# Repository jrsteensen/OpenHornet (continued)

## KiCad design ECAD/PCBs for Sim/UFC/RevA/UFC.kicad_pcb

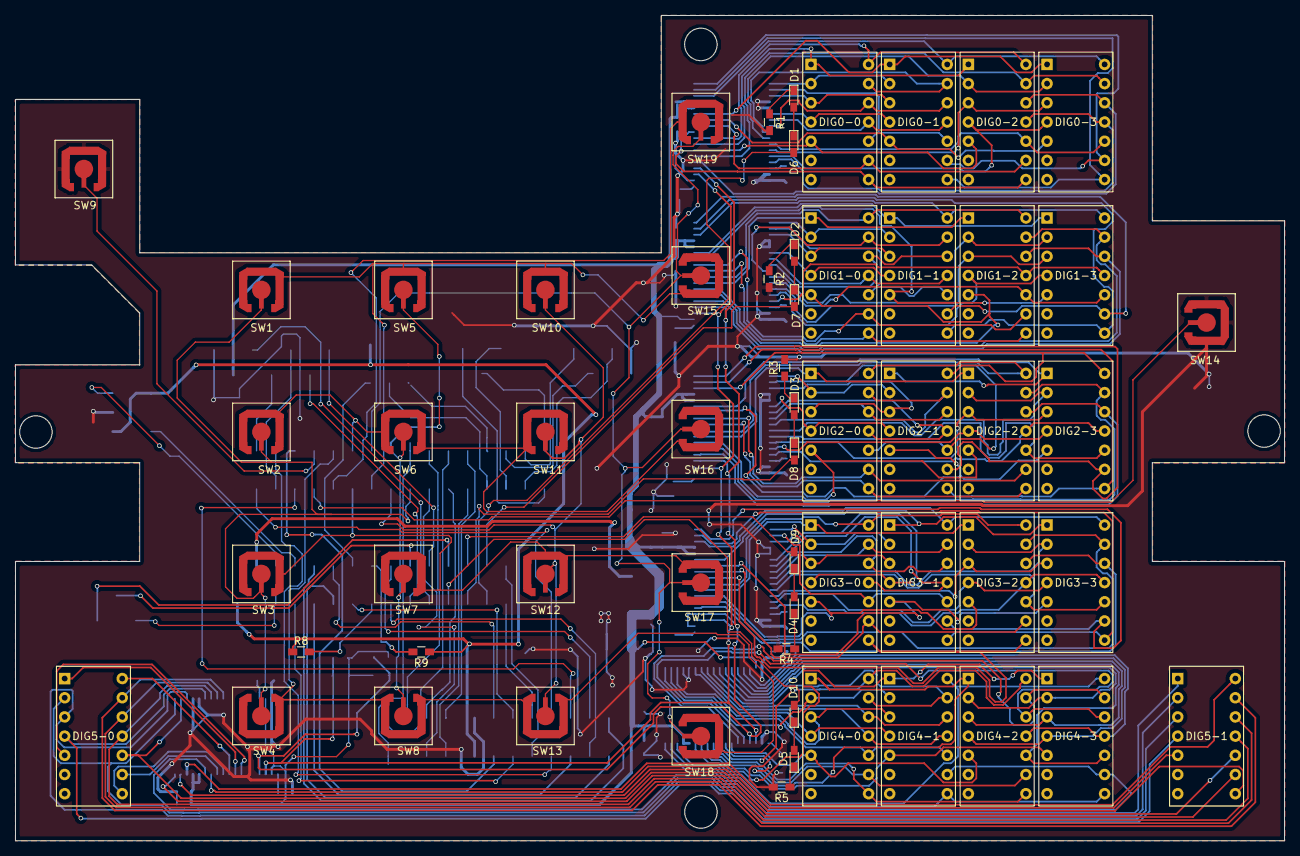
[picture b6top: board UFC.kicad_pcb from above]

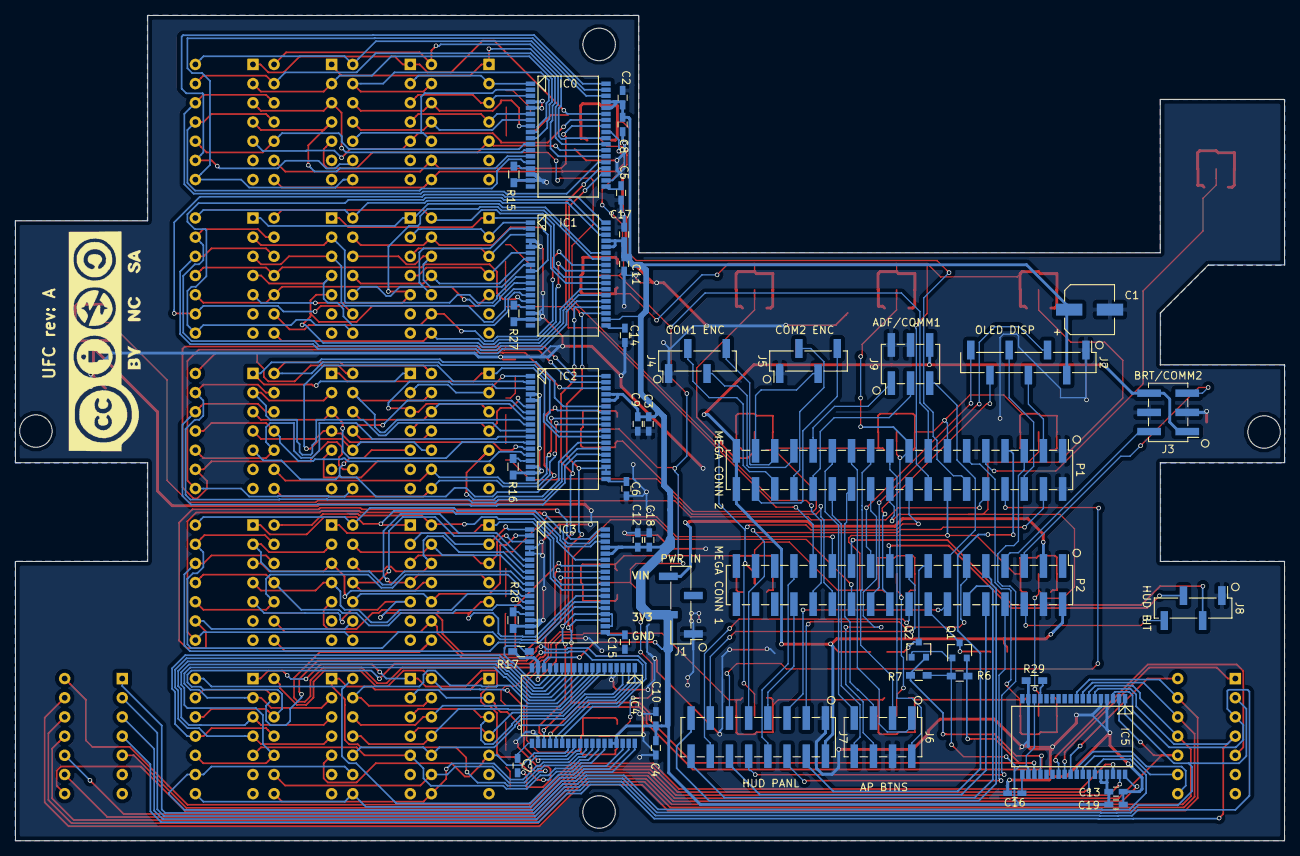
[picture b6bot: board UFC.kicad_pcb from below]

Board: 2 copper layers, 168.0 x 109.2 mm, 108 parts (46 on the bottom side), 223 nets.

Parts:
C1: 220uF; CP_Elec_6.3x7.7
C2, C3, C4, C11, C12, C13: 47uF; C_0603_HandSoldering
C5, C6, C7, C14, C15, C16: 27pF; C_0603_HandSoldering
C8, C9, C10, C17, C18, C19: 100nF; C_0603_HandSoldering
D1, D2, D3, D4, D5, D6, D7, D8, D9, D10: WP914GDT; LED_0603_HandSoldering
DIG0-0, DIG0-1, DIG0-2, DIG0-3, DIG1-0, DIG1-1, DIG1-2, DIG1-3, DIG2-0, DIG2-1, DIG2-2, DIG2-3, DIG3-0, DIG3-1, DIG3-2, DIG3-3, DIG4-0, DIG4-1, DIG4-2, DIG4-3, DIG5-0, DIG5-1: LTP-305G
IC0, IC1, IC2, IC3, IC4, IC5: MAX6953
J1: PWR IN; Pin_Header_Straight_1x04_Pitch2.54mm_SMD_Pin1Left
J2: OLED DISP; Pin_Header_Straight_1x07_Pitch2.54mm_SMD_Pin1Left
J3: BRT/COMM2; Pin_Header_Straight_2x03_Pitch2.54mm_SMD
J4: COM1 ENC; Pin_Header_Straight_1x04_Pitch2.54mm_SMD_Pin1Left
J5: COM2 ENC; Pin_Header_Straight_1x04_Pitch2.54mm_SMD_Pin1Left
J6: AP BTNS; Pin_Header_Straight_2x04_Pitch2.54mm_SMD
J7: HUD PANL; Pin_Header_Straight_2x08_Pitch2.54mm_SMD
J8: HUD BIT; Pin_Header_Straight_1x04_Pitch2.54mm_SMD_Pin1Left
J9: ADF/COMM1; Pin_Header_Straight_2x03_Pitch2.54mm_SMD
MK1, MK2, MK3, MK4: Mounting_Hole; MountingHole_4.3mm_M4
P1: MEGA CONN 2; Pin_Header_Straight_2x18_Pitch2.54mm_SMD
P2: MEGA CONN 1; Pin_Header_Straight_2x18_Pitch2.54mm_SMD
Q1, Q2: BSS138; SOT-23
R1, R2, R3, R4, R5: 33; R_0603_HandSoldering
R6, R7, R8, R9: 10k; R_0603_HandSoldering
R15, R16, R17, R27, R28, R29: 53.6k; R_0603_HandSoldering
SW1: 1; SWITCH_SNAP_DOME_6.3mm_DIA_SINGLE_SIDE_PCB
SW2: 4; SWITCH_SNAP_DOME_6.3mm_DIA_SINGLE_SIDE_PCB
SW3: 7; SWITCH_SNAP_DOME_6.3mm_DIA_SINGLE_SIDE_PCB
SW4: CLR; SWITCH_SNAP_DOME_6.3mm_DIA_SINGLE_SIDE_PCB
SW5: 2; SWITCH_SNAP_DOME_6.3mm_DIA_SINGLE_SIDE_PCB
SW6: 5; SWITCH_SNAP_DOME_6.3mm_DIA_SINGLE_SIDE_PCB
SW7: 8; SWITCH_SNAP_DOME_6.3mm_DIA_SINGLE_SIDE_PCB
SW8: ~0; SWITCH_SNAP_DOME_6.3mm_DIA_SINGLE_SIDE_PCB
SW9: I/P; SWITCH_SNAP_DOME_6.3mm_DIA_SINGLE_SIDE_PCB
SW10: 3; SWITCH_SNAP_DOME_6.3mm_DIA_SINGLE_SIDE_PCB
SW11: 6; SWITCH_SNAP_DOME_6.3mm_DIA_SINGLE_SIDE_PCB
SW12: 9; SWITCH_SNAP_DOME_6.3mm_DIA_SINGLE_SIDE_PCB
SW13: ENT; SWITCH_SNAP_DOME_6.3mm_DIA_SINGLE_SIDE_PCB
SW14: EMCON; SWITCH_SNAP_DOME_6.3mm_DIA_SINGLE_SIDE_PCB
SW15: OPT2; SWITCH_SNAP_DOME_6.3mm_DIA_SINGLE_SIDE_PCB
SW16: OPT3; SWITCH_SNAP_DOME_6.3mm_DIA_SINGLE_SIDE_PCB
SW17: OPT4; SWITCH_SNAP_DOME_6.3mm_DIA_SINGLE_SIDE_PCB
SW18: OPT5; SWITCH_SNAP_DOME_6.3mm_DIA_SINGLE_SIDE_PCB
SW19: OPT1; SWITCH_SNAP_DOME_6.3mm_DIA_SINGLE_SIDE_PCB

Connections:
+3V3: C1.1, C2.1, C3.1, C4.1, C8.1, C9.1, C10.1, C11.1, C12.1, C13.1, C17.1, C18.1, C19.1, IC0.32, IC0.33, IC1.20, IC1.32, IC1.33, IC2.32, IC2.33, IC3.32, IC3.33, IC4.16, IC4.32, IC4.33, IC5.16, IC5.20, IC5.32, IC5.33, J1.2, J2.2, Q1.1, Q2.1, R6.1, R7.1
+5V: J3.1, J3.6, J7.2, J9.6, P1.35, P1.36, P2.2, R8.1, R9.1
/0(Rx0): J7.7, P2.30
/1(Tx0): J7.8, P2.29
/2(**): D6.2, P2.28
/3(**): D7.2, P2.27
/4(**): D8.2, P2.26
/5(**): D9.2, P2.25
/6(**): D10.2, P2.24
/7(**): J8.2, P2.23
/8(**): J2.3, P2.22
/9(**): J2.7, P2.21
/10(**): J2.6, P2.20
/11(**): J8.3, P2.19
/12(**): J7.14, P2.18
/13(**): J7.13, P2.17
/22: J9.1, P1.27
/23: J9.3, P1.28
/24: J4.4, P1.31
/25: J4.2, P1.32
/26: J4.3, P1.29
/27: J5.2, P1.30
/28: J5.3, P1.33
/29: J5.4, P1.34
/30: J6.7, P1.25
/31: J6.8, P1.26
/32: J6.3, P1.21
/33: J6.5, P1.24
/34: J6.1, P1.23
/35: J6.6, P1.22
/36: J6.2, P1.19
/37: P1.20, SW1.1, SW2.1, SW3.1, SW4.1
/38: P1.17, SW5.1, SW6.1, SW7.1, SW8.1
/39: P1.18, SW10.1, SW11.1, SW12.1, SW13.1
/40: P1.15, SW15.1, SW16.1, SW17.1, SW18.1, SW19.1
/41: P1.16, SW1.2, SW5.2, SW10.2, SW15.2
/42: P1.13, SW2.2, SW6.2, SW11.2, SW16.2
/43: P1.14, SW3.2, SW7.2, SW12.2, SW17.2
/44: P1.11, SW4.2, SW8.2, SW13.2, SW18.2
/45: P1.12, SW19.2
/46: P1.9, SW9.1
/47: P1.10, SW14.1
/48: J7.4, P1.7
/49: J7.11, P1.8
/50(MISO): J7.10, P1.5
/51(MOSI): J2.5, P1.6
/52(SCK): J2.4, P1.3
/53(SS): J7.9, P1.4
/A0: J3.2, P2.7
/A1: J3.5, P2.5
/A2: J9.5, P2.13
/A3: J7.3, P2.11
/A4: J7.12, P2.10
/A5: J7.5, P2.14
/A6: J7.6, P2.8
/A7: J7.16, P2.12
/A8: J7.15, P2.9
/A9: J8.4, P2.6
/IC0-O0: DIG0-0.2, DIG0-1.2, IC0.1
/IC0-O1: DIG0-0.12, DIG0-1.12, IC0.2
/IC0-O2: DIG0-0.3, DIG0-1.3, IC0.3
/IC0-O3: DIG0-0.4, DIG0-1.4, IC0.6
/IC0-O4: DIG0-0.11, DIG0-1.11, IC0.7
/IC0-O5: DIG0-0.10, DIG0-1.10, IC0.8
/IC0-O6: DIG0-0.9, DIG0-1.9, IC0.9
/IC0-O7: DIG0-2.2, DIG0-3.2, IC0.10
/IC0-O8: DIG0-2.12, DIG0-3.12, IC0.11
/IC0-O9: DIG0-2.3, DIG0-3.3, IC0.12
/IC0-O10: DIG0-2.4, DIG0-3.4, IC0.13
/IC0-O11: DIG0-2.11, DIG0-3.11, IC0.14
/IC0-O12: DIG0-2.10, DIG0-3.10, IC0.23
/IC0-O13: DIG0-2.9, DIG0-3.9, IC0.24
/IC0-O14: DIG0-0.5, DIG0-2.5, IC0.25
/IC0-O15: DIG0-0.1, DIG0-2.1, IC0.26
/IC0-O16: DIG0-0.8, DIG0-2.8, IC0.27
/IC0-O17: DIG0-0.14, DIG0-2.14, IC0.28
/IC0-O18: DIG0-0.13, DIG0-2.13, IC0.29
/IC0-O19: DIG0-1.5, DIG0-3.5, IC0.30
/IC0-O20: DIG0-1.1, DIG0-3.1, IC0.31
/IC0-O21: DIG0-1.8, DIG0-3.8, IC0.34
/IC0-O22: DIG0-1.14, DIG0-3.14, IC0.35
/IC0-O23: DIG0-1.13, DIG0-3.13, IC0.36
/IC1-O0: DIG1-0.2, DIG1-1.2, IC1.1
/IC1-O1: DIG1-0.12, DIG1-1.12, IC1.2
/IC1-O2: DIG1-0.3, DIG1-1.3, IC1.3
/IC1-O3: DIG1-0.4, DIG1-1.4, IC1.6
/IC1-O4: DIG1-0.11, DIG1-1.11, IC1.7
/IC1-O5: DIG1-0.10, DIG1-1.10, IC1.8
/IC1-O6: DIG1-0.9, DIG1-1.9, IC1.9
/IC1-O7: DIG1-2.2, DIG1-3.2, IC1.10
/IC1-O8: DIG1-2.12, DIG1-3.12, IC1.11
/IC1-O9: DIG1-2.3, DIG1-3.3, IC1.12
/IC1-O10: DIG1-2.4, DIG1-3.4, IC1.13
/IC1-O11: DIG1-2.11, DIG1-3.11, IC1.14
/IC1-O12: DIG1-2.10, DIG1-3.10, IC1.23
/IC1-O13: DIG1-2.9, DIG1-3.9, IC1.24
/IC1-O14: DIG1-0.5, DIG1-2.5, IC1.25
/IC1-O15: DIG1-0.1, DIG1-2.1, IC1.26
/IC1-O16: DIG1-0.8, DIG1-2.8, IC1.27
/IC1-O17: DIG1-0.14, DIG1-2.14, IC1.28
/IC1-O18: DIG1-0.13, DIG1-2.13, IC1.29
/IC1-O19: DIG1-1.5, DIG1-3.5, IC1.30
/IC1-O20: DIG1-1.1, DIG1-3.1, IC1.31
/IC1-O21: DIG1-1.8, DIG1-3.8, IC1.34
/IC1-O22: DIG1-1.14, DIG1-3.14, IC1.35
/IC1-O23: DIG1-1.13, DIG1-3.13, IC1.36
/IC2-O0: DIG2-0.2, DIG2-1.2, IC2.1
/IC2-O1: DIG2-0.12, DIG2-1.12, IC2.2
/IC2-O2: DIG2-0.3, DIG2-1.3, IC2.3
/IC2-O3: DIG2-0.4, DIG2-1.4, IC2.6
/IC2-O4: DIG2-0.11, DIG2-1.11, IC2.7
/IC2-O5: DIG2-0.10, DIG2-1.10, IC2.8
/IC2-O6: DIG2-0.9, DIG2-1.9, IC2.9
/IC2-O7: DIG2-2.2, DIG2-3.2, IC2.10
/IC2-O8: DIG2-2.12, DIG2-3.12, IC2.11
/IC2-O9: DIG2-2.3, DIG2-3.3, IC2.12
/IC2-O10: DIG2-2.4, DIG2-3.4, IC2.13
/IC2-O11: DIG2-2.11, DIG2-3.11, IC2.14
/IC2-O12: DIG2-2.10, DIG2-3.10, IC2.23
/IC2-O13: DIG2-2.9, DIG2-3.9, IC2.24
/IC2-O14: DIG2-0.5, DIG2-2.5, IC2.25
/IC2-O15: DIG2-0.1, DIG2-2.1, IC2.26
/IC2-O16: DIG2-0.8, DIG2-2.8, IC2.27
/IC2-O17: DIG2-0.14, DIG2-2.14, IC2.28
/IC2-O18: DIG2-0.13, DIG2-2.13, IC2.29
/IC2-O19: DIG2-1.5, DIG2-3.5, IC2.30
/IC2-O20: DIG2-1.1, DIG2-3.1, IC2.31
/IC2-O21: DIG2-1.8, DIG2-3.8, IC2.34
/IC2-O22: DIG2-1.14, DIG2-3.14, IC2.35
/IC2-O23: DIG2-1.13, DIG2-3.13, IC2.36
/IC3-O0: DIG3-0.2, DIG3-1.2, IC3.1
/IC3-O1: DIG3-0.12, DIG3-1.12, IC3.2
/IC3-O2: DIG3-0.3, DIG3-1.3, IC3.3
/IC3-O3: DIG3-0.4, DIG3-1.4, IC3.6
/IC3-O4: DIG3-0.11, DIG3-1.11, IC3.7
/IC3-O5: DIG3-0.10, DIG3-1.10, IC3.8
/IC3-O6: DIG3-0.9, DIG3-1.9, IC3.9
/IC3-O7: DIG3-2.2, DIG3-3.2, IC3.10
/IC3-O8: DIG3-2.12, DIG3-3.12, IC3.11
/IC3-O9: DIG3-2.3, DIG3-3.3, IC3.12
/IC3-O10: DIG3-2.4, DIG3-3.4, IC3.13
/IC3-O11: DIG3-2.11, DIG3-3.11, IC3.14
/IC3-O12: DIG3-2.10, DIG3-3.10, IC3.23
/IC3-O13: DIG3-2.9, DIG3-3.9, IC3.24
/IC3-O14: DIG3-0.5, DIG3-2.5, IC3.25
/IC3-O15: DIG3-0.1, DIG3-2.1, IC3.26
/IC3-O16: DIG3-0.8, DIG3-2.8, IC3.27
/IC3-O17: DIG3-0.14, DIG3-2.14, IC3.28
/IC3-O18: DIG3-0.13, DIG3-2.13, IC3.29
/IC3-O19: DIG3-1.5, DIG3-3.5, IC3.30
/IC3-O20: DIG3-1.1, DIG3-3.1, IC3.31
/IC3-O21: DIG3-1.8, DIG3-3.8, IC3.34
/IC3-O22: DIG3-1.14, DIG3-3.14, IC3.35
/IC3-O23: DIG3-1.13, DIG3-3.13, IC3.36
/IC4-O0: DIG4-0.2, DIG4-1.2, IC4.1
/IC4-O1: DIG4-0.12, DIG4-1.12, IC4.2
/IC4-O2: DIG4-0.3, DIG4-1.3, IC4.3
/IC4-O3: DIG4-0.4, DIG4-1.4, IC4.6
/IC4-O4: DIG4-0.11, DIG4-1.11, IC4.7
/IC4-O5: DIG4-0.10, DIG4-1.10, IC4.8
/IC4-O6: DIG4-0.9, DIG4-1.9, IC4.9
/IC4-O7: DIG4-2.2, DIG4-3.2, IC4.10
/IC4-O8: DIG4-2.12, DIG4-3.12, IC4.11
/IC4-O9: DIG4-2.3, DIG4-3.3, IC4.12
/IC4-O10: DIG4-2.4, DIG4-3.4, IC4.13
/IC4-O11: DIG4-2.11, DIG4-3.11, IC4.14
/IC4-O12: DIG4-2.10, DIG4-3.10, IC4.23
/IC4-O13: DIG4-2.9, DIG4-3.9, IC4.24
/IC4-O14: DIG4-0.5, DIG4-2.5, IC4.25
/IC4-O15: DIG4-0.1, DIG4-2.1, IC4.26
/IC4-O16: DIG4-0.8, DIG4-2.8, IC4.27
/IC4-O17: DIG4-0.14, DIG4-2.14, IC4.28
/IC4-O18: DIG4-0.13, DIG4-2.13, IC4.29
/IC4-O19: DIG4-1.5, DIG4-3.5, IC4.30
/IC4-O20: DIG4-1.1, DIG4-3.1, IC4.31
/IC4-O21: DIG4-1.8, DIG4-3.8, IC4.34
/IC4-O22: DIG4-1.14, DIG4-3.14, IC4.35
/IC4-O23: DIG4-1.13, DIG4-3.13, IC4.36
/IC5-O0: DIG5-0.2, DIG5-1.2, IC5.1
/IC5-O1: DIG5-0.12, DIG5-1.12, IC5.2
/IC5-O2: DIG5-0.3, DIG5-1.3, IC5.3
/IC5-O3: DIG5-0.4, DIG5-1.4, IC5.6
/IC5-O4: DIG5-0.11, DIG5-1.11, IC5.7
/IC5-O5: DIG5-0.10, DIG5-1.10, IC5.8
/IC5-O6: DIG5-0.9, DIG5-1.9, IC5.9
/IC5-O14: DIG5-0.5, IC5.25
/IC5-O15: DIG5-0.1, IC5.26
/IC5-O16: DIG5-0.8, IC5.27
/IC5-O17: DIG5-0.14, IC5.28
/IC5-O18: DIG5-0.13, IC5.29
/IC5-O19: DIG5-1.5, IC5.30
/IC5-O20: DIG5-1.1, IC5.31
/IC5-O21: DIG5-1.8, IC5.34
/IC5-O22: DIG5-1.14, IC5.35
/IC5-O23: DIG5-1.13, IC5.36
/SCL: IC0.22, IC1.22, IC2.22, IC3.20, IC3.22, IC4.22, IC5.22, Q2.2, R7.2
/SCL5v: P2.15, Q2.3, R9.2
/SDA: IC0.21, IC1.21, IC2.20, IC2.21, IC3.21, IC4.21, IC5.21, Q1.2, R6.2
/SDA5v: P2.16, Q1.3, R8.2
/Vin: J1.4, P2.3
GND: C1.2, C2.2, C3.2, C4.2, C5.2, C6.2, C7.2, C8.2, C9.2, C10.2, C11.2, C12.2, C13.2, C14.2, C15.2, C16.2, C17.2, C18.2, C19.2, IC0.4, IC0.5, IC0.16, IC0.17, IC0.20, IC1.4, IC1.5, IC1.16, IC1.17, IC2.4, IC2.5, IC2.16, IC2.17, IC3.4, IC3.5, IC3.16, IC3.17, IC4.4, IC4.5, IC4.17, IC4.20, IC5.4, IC5.5, IC5.17, J1.1, J2.1, J3.3, J3.4, J4.1, J5.1, J6.4, J7.1, J8.1, J9.2, J9.4, P1.1, P1.2, P2.4, R1.2, R2.2, R3.2, R4.2, R5.2, R15.2, R16.2, R17.2, R27.2, R28.2, R29.2, SW9.2, SW14.2
unnamed: C5.1, IC0.19
unnamed: C6.1, IC2.19
unnamed: C7.1, IC4.19
unnamed: C14.1, IC1.19
unnamed: C15.1, IC3.19
unnamed: C16.1, IC5.19
unnamed: D1.1, R1.1
unnamed: D1.2, D6.1
unnamed: D2.1, R2.1
unnamed: D2.2, D7.1
unnamed: D3.1, R3.1
unnamed: D3.2, D8.1
unnamed: D4.1, R4.1
unnamed: D4.2, D9.1
unnamed: D5.1, R5.1
unnamed: D5.2, D10.1
unnamed: IC0.15, R15.1
unnamed: IC1.15, R27.1
unnamed: IC2.15, R16.1
unnamed: IC3.15, R28.1
unnamed: IC4.15, R17.1
unnamed: IC5.15, R29.1
